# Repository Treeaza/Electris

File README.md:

# Electris
 Hardware and software for a custom arcade machine

Copyright Jasper Rubin, 2021
All rights reserved

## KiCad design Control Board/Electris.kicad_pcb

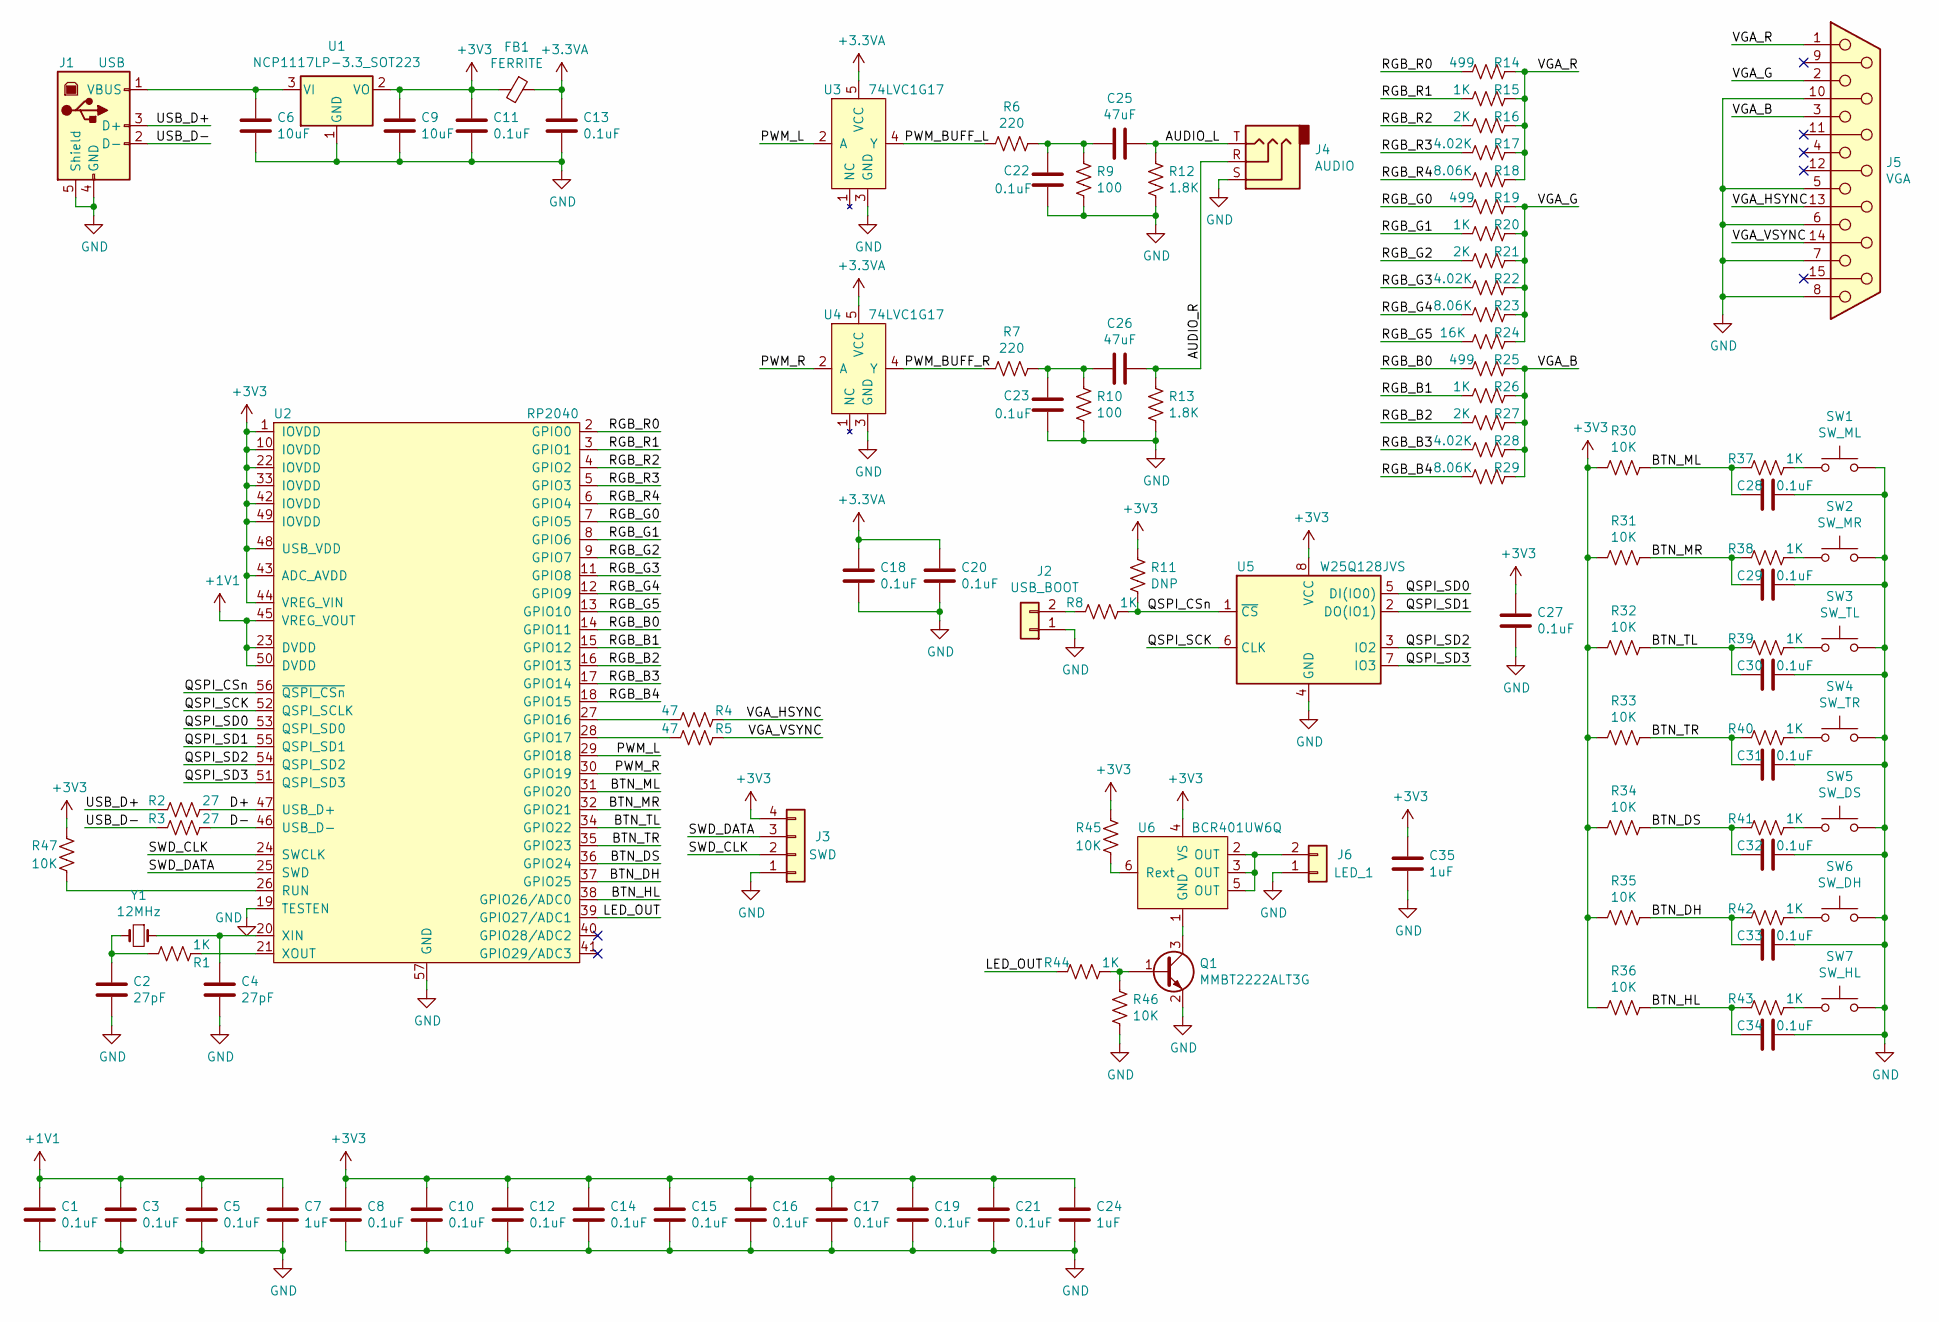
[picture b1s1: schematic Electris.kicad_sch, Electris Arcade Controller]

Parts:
C1, C3, C5, C8, C10, C11, C12, C13, C14, C15, C16, C17, C18, C19, C20, C21, C22, C23, C27, C28, C29, C30, C31, C32, C33, C34: 0.1uF; C_0603_1608Metric_Pad1.08x0.95mm_HandSolder
C2, C4: 27pF; C_0603_1608Metric_Pad1.08x0.95mm_HandSolder
C6, C9: 10uF; C_0805_2012Metric_Pad1.18x1.45mm_HandSolder
C7, C24, C35: 1uF; C_0603_1608Metric_Pad1.08x0.95mm_HandSolder
C25, C26: 47uF; C_0805_2012Metric_Pad1.18x1.45mm_HandSolder
FB1: FERRITE; L_0603_1608Metric_Pad1.05x0.95mm_HandSolder
J1: USB; USB_B_OST_USB-B1HSxx_Horizontal; Digikey UJ2-BH-W1-TH
J2: USB_BOOT; SolderJumper-2_P1.3mm_Open_RoundedPad1.0x1.5mm
J3: SWD; PinHeader_1x04_P2.54mm_Vertical
J4: AUDIO; Connector_CUI_SJ1-2503A; Digikey SJ1-2503A
J5: VGA; Connector_Amphenol_ICD15S13E4GX00LF; Digikey ICD15S13E4GX00LF
J6: LED_1; JST_EH_B2B-EH-A_1x02_P2.50mm_Vertical
Q1: MMBT2222ALT3G; TSOT-23_HandSoldering
R1, R8, R15, R20, R26, R37, R38, R39, R40, R41, R42, R43, R44: 1K; R_0603_1608Metric_Pad0.98x0.95mm_HandSolder
R2, R3: 27; R_0805_2012Metric_Pad1.20x1.40mm_HandSolder
R4, R5: 47; R_0603_1608Metric_Pad0.98x0.95mm_HandSolder
R6, R7: 220; R_0805_2012Metric_Pad1.20x1.40mm_HandSolder
R9, R10: 100; R_0805_2012Metric_Pad1.20x1.40mm_HandSolder
R11: DNP; R_0603_1608Metric_Pad0.98x0.95mm_HandSolder
R12, R13: 1.8K; R_0805_2012Metric_Pad1.20x1.40mm_HandSolder
R14, R19, R25: 499; R_0603_1608Metric_Pad0.98x0.95mm_HandSolder
R16, R21, R27: 2K; R_0603_1608Metric_Pad0.98x0.95mm_HandSolder
R17, R22, R28: 4.02K; R_0603_1608Metric_Pad0.98x0.95mm_HandSolder
R18, R23, R29: 8.06K; R_0603_1608Metric_Pad0.98x0.95mm_HandSolder
R24: 16K; R_0603_1608Metric_Pad0.98x0.95mm_HandSolder
R30, R31, R32, R33, R34, R35, R36, R45, R46, R47: 10K; R_0603_1608Metric_Pad0.98x0.95mm_HandSolder
SW1: SW_ML; JST_EH_B2B-EH-A_1x02_P2.50mm_Vertical
SW2: SW_MR; JST_EH_B2B-EH-A_1x02_P2.50mm_Vertical
SW3: SW_TL; JST_EH_B2B-EH-A_1x02_P2.50mm_Vertical
SW4: SW_TR; JST_EH_B2B-EH-A_1x02_P2.50mm_Vertical
SW5: SW_DS; JST_EH_B2B-EH-A_1x02_P2.50mm_Vertical
SW6: SW_DH; JST_EH_B2B-EH-A_1x02_P2.50mm_Vertical
SW7: SW_HL; JST_EH_B2B-EH-A_1x02_P2.50mm_Vertical
U1: NCP1117LP-3.3_SOT223; SOT-223-3_TabPin2; Digikey NCP1117LPST33T3G
U2: RP2040; QFN_RP2040
U3, U4: 74LVC1G17; TSOT-23-5_HandSoldering
U5: W25Q128JVS; SOIC-8_5.23x5.23mm_P1.27mm
U6: BCR401UW6Q; SOT-23-6_Handsoldering
Y1: 12MHz; Crystal_SMD_HC49-SD; Digikey ABLS7M-12.000MHZ-B-2-T

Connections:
+1V1: C1.1, C3.1, C5.1, C7.1, U2.23 (DVDD), U2.45 (VREG_VOUT), U2.50 (DVDD)
+3.3VA: C13.1, C18.1, C20.1, FB1.1, U3.5 (VCC), U4.5 (VCC)
+3V3: C8.1, C9.1, C10.1, C11.1, C12.1, C14.1, C15.1, C16.1, C17.1, C19.1, C21.1, C24.1, C27.1, C35.1, FB1.2, J3.4, R11.1, R30.2, R31.2, R32.2, R33.2, R34.2, R35.2, R36.2, R45.1, R47.1, U1.2 (VO), U2.1 (IOVDD), U2.10 (IOVDD), U2.22 (IOVDD), U2.33 (IOVDD), U2.42 (IOVDD), U2.43 (ADC_AVDD), U2.44 (VREG_VIN), U2.48 (USB_VDD), U2.49 (IOVDD), U5.8 (VCC), U6.4 (VS)
/AUDIO_L: C25.1, J4.T, R12.1
/AUDIO_R: C26.1, J4.R, R13.1
/BTN_DH: C33.2, R35.1, R42.2, U2.37 (GPIO25)
/BTN_DS: C32.2, R34.1, R41.2, U2.36 (GPIO24)
/BTN_HL: C34.2, R36.1, R43.2, U2.38 (GPIO26/ADC0)
/BTN_ML: C28.2, R30.1, R37.2, U2.31 (GPIO20)
/BTN_MR: C29.2, R31.1, R38.2, U2.32 (GPIO21)
/BTN_TL: C30.2, R32.1, R39.2, U2.34 (GPIO22)
/BTN_TR: C31.2, R33.1, R40.2, U2.35 (GPIO23)
/D+: R2.1, U2.47 (USB_D+)
/D-: R3.1, U2.46 (USB_D-)
/LED_OUT: R44.2, U2.39 (GPIO27/ADC1)
/PWM_BUFF_L: R6.2, U3.4 (Y)
/PWM_BUFF_R: R7.2, U4.4 (Y)
/PWM_L: U2.29 (GPIO18), U3.2 (A)
/PWM_R: U2.30 (GPIO19), U4.2 (A)
/QSPI_CSn: R8.1, R11.2, U2.56 (~QSPI_CSn), U5.1 (~CS)
/QSPI_SCK: U2.52 (QSPI_SCLK), U5.6 (CLK)
/QSPI_SD0: U2.53 (QSPI_SD0), U5.5 (DI(IO0))
/QSPI_SD1: U2.55 (QSPI_SD1), U5.2 (DO(IO1))
/QSPI_SD2: U2.54 (QSPI_SD2), U5.3 (IO2)
/QSPI_SD3: U2.51 (QSPI_SD3), U5.7 (IO3)
/RGB_B0: R25.2, U2.14 (GPIO11)
/RGB_B1: R26.2, U2.15 (GPIO12)
/RGB_B2: R27.2, U2.16 (GPIO13)
/RGB_B3: R28.2, U2.17 (GPIO14)
/RGB_B4: R29.2, U2.18 (GPIO15)
/RGB_G0: R19.2, U2.7 (GPIO5)
/RGB_G1: R20.2, U2.8 (GPIO6)
/RGB_G2: R21.2, U2.9 (GPIO7)
/RGB_G3: R22.2, U2.11 (GPIO8)
/RGB_G4: R23.2, U2.12 (GPIO9)
/RGB_G5: R24.2, U2.13 (GPIO10)
/RGB_R0: R14.2, U2.2 (GPIO0)
/RGB_R1: R15.2, U2.3 (GPIO1)
/RGB_R2: R16.2, U2.4 (GPIO2)
/RGB_R3: R17.2, U2.5 (GPIO3)
/RGB_R4: R18.2, U2.6 (GPIO4)
/SWD_CLK: J3.2, U2.24 (SWCLK)
/SWD_DATA: J3.3, U2.25 (SWD)
/USB_D+: J1.3 (D+), R2.2
/USB_D-: J1.2 (D-), R3.2
/VGA_B: J5.3, R25.1, R26.1, R27.1, R28.1, R29.1
/VGA_G: J5.2, R19.1, R20.1, R21.1, R22.1, R23.1, R24.1
/VGA_HSYNC: J5.13, R4.1
/VGA_R: J5.1, R14.1, R15.1, R16.1, R17.1, R18.1
/VGA_VSYNC: J5.14, R5.1
GND: C1.2, C2.2, C3.2, C4.2, C5.2, C6.2, C7.2, C8.2, C9.2, C10.2, C11.2, C12.2, C13.2, C14.2, C15.2, C16.2, C17.2, C18.2, C19.2, C20.2, C21.2, C22.2, C23.2, C24.2, C27.2, C28.1, C29.1, C30.1, C31.1, C32.1, C33.1, C34.1, C35.2, J1.4 (GND), J1.5 (Shield), J2.1, J3.1, J4.S, J5.5, J5.6, J5.7, J5.8, J5.10, J6.1, Q1.2 (E), R9.2, R10.2, R12.2, R13.2, R46.2, SW1.2, SW2.2, SW3.2, SW4.2, SW5.2, SW6.2, SW7.2, U1.1 (GND), U2.19 (TESTEN), U2.57 (GND), U3.3 (GND), U4.3 (GND), U5.4 (GND)
unnamed: C2.1, R1.2, Y1.2
unnamed: C4.1, U2.20 (XIN), Y1.1
unnamed: C6.1, J1.1 (VBUS), U1.3 (VI)
unnamed: C22.1, C25.2, R6.1, R9.1
unnamed: C23.1, C26.2, R7.1, R10.1
unnamed: J2.2, R8.2
unnamed: J6.2, U6.2 (OUT), U6.3 (OUT), U6.5 (OUT)
unnamed: Q1.1 (B), R44.1, R46.1
unnamed: Q1.3 (C), U6.1 (GND)
unnamed: R1.1, U2.21 (XOUT)
unnamed: R4.2, U2.27 (GPIO16)
unnamed: R5.2, U2.28 (GPIO17)
unnamed: R37.1, SW1.1
unnamed: R38.1, SW2.1
unnamed: R39.1, SW3.1
unnamed: R40.1, SW4.1
unnamed: R41.1, SW5.1
unnamed: R42.1, SW6.1
unnamed: R43.1, SW7.1
unnamed: R45.2, U6.6 (Rext)
unnamed: R47.2, U2.26 (RUN)

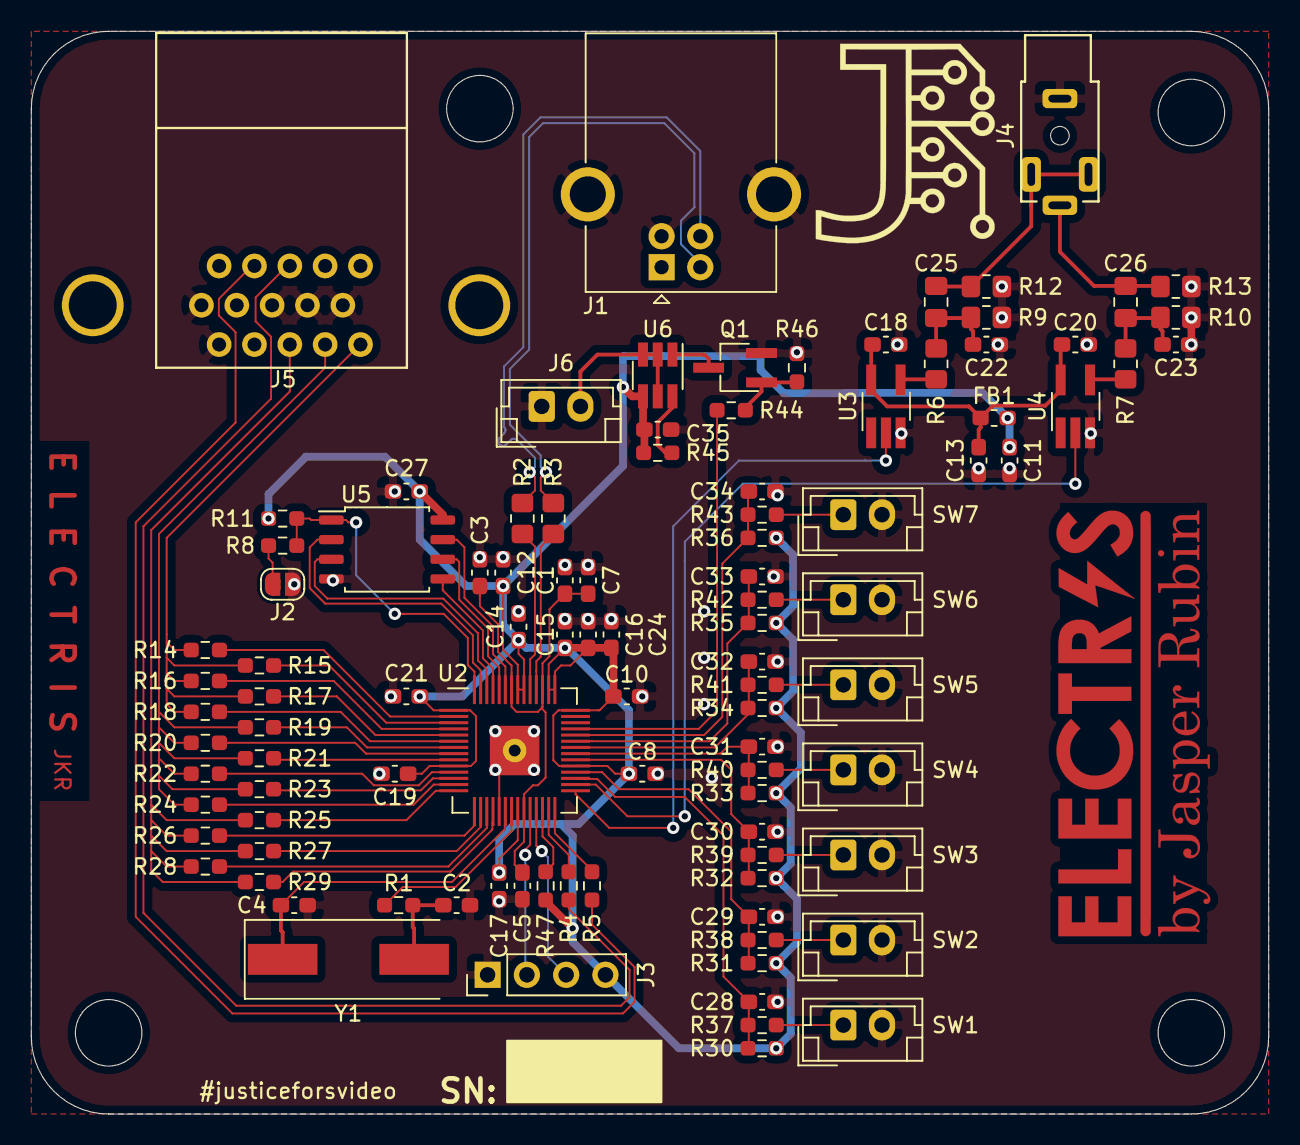
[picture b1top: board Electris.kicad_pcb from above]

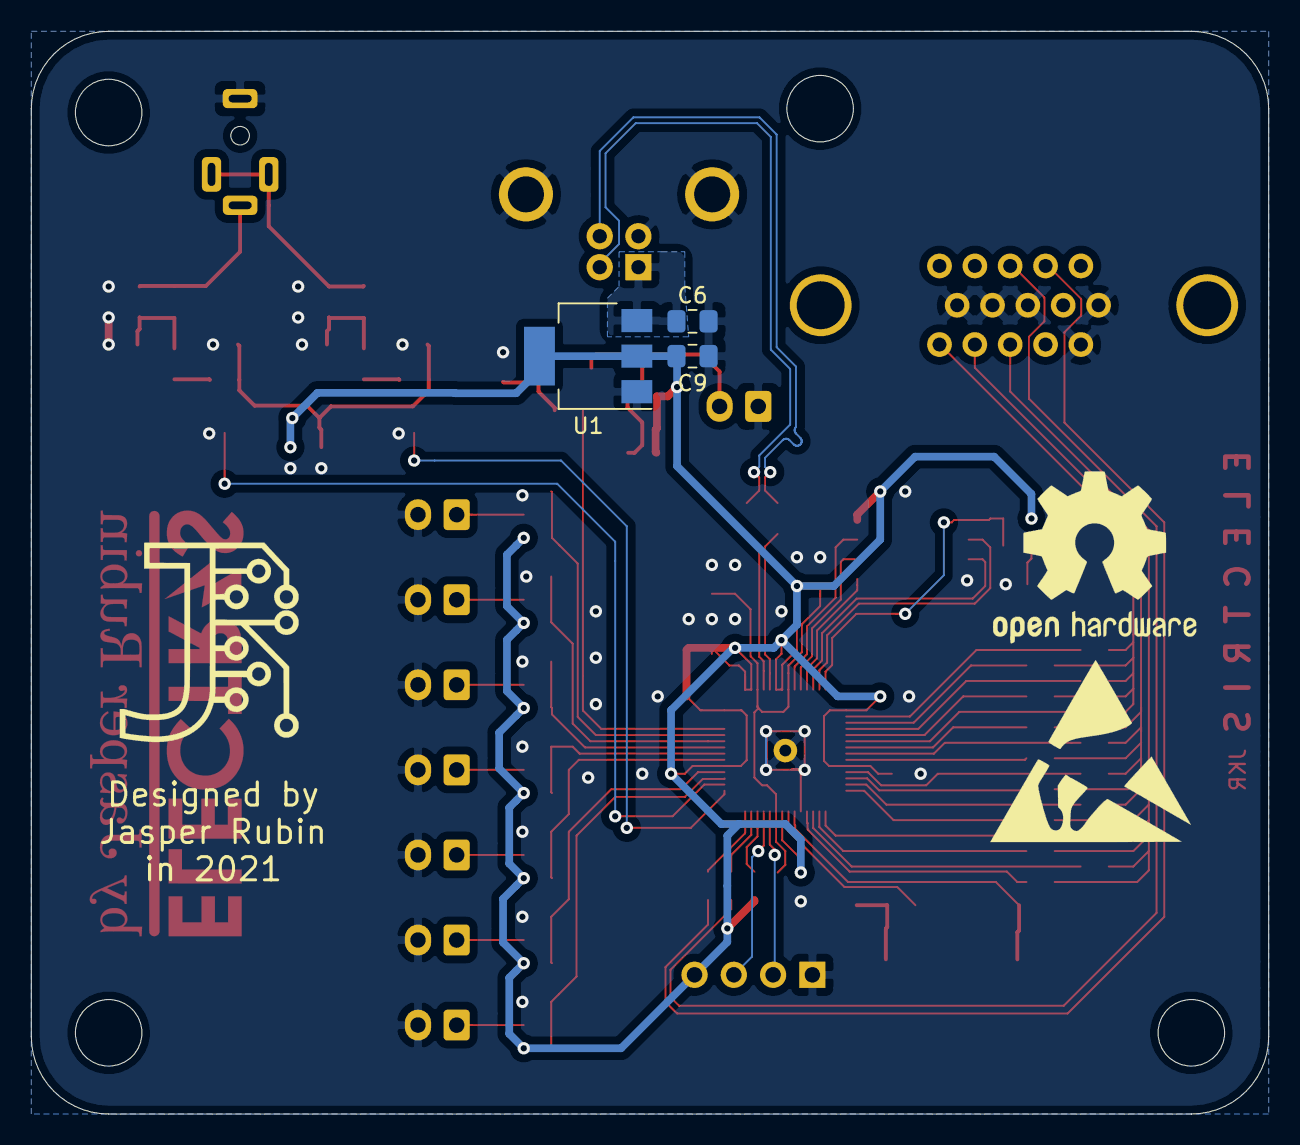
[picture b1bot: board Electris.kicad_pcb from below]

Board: 2 copper layers, 80.0 x 70.0 mm, 104 parts (3 on the bottom side), 72 nets.

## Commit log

2021-03-15 Create control board project
2021-05-06 Complete schematic
2021-08-07 Switched to RP2040, finished schematic, started layout.
2021-08-07 Routing
2021-08-08 Finish routing
2021-08-11 Board ready for production
2021-12-31 Work on software
2022-02-03 Most of the game model implemented
2022-08-30 ...something
2024-03-30 Clean up
